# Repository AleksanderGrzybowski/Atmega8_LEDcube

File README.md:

This is a 4x4x4 LED cube made just for the fun of creating it. Cube has been built using the cheapest LEDs on tme.eu, 64 of them, multiplexed: 16 N-driven columns and 4 P-driven layers. Maximum constant and actual diode current is ~50 mA, which makes sure that they won't fail even when multiplexing hangs in the middle while programming. Driver board is made with 3 '595 shift registers, CPU board is using typical Atmega8 family chip.

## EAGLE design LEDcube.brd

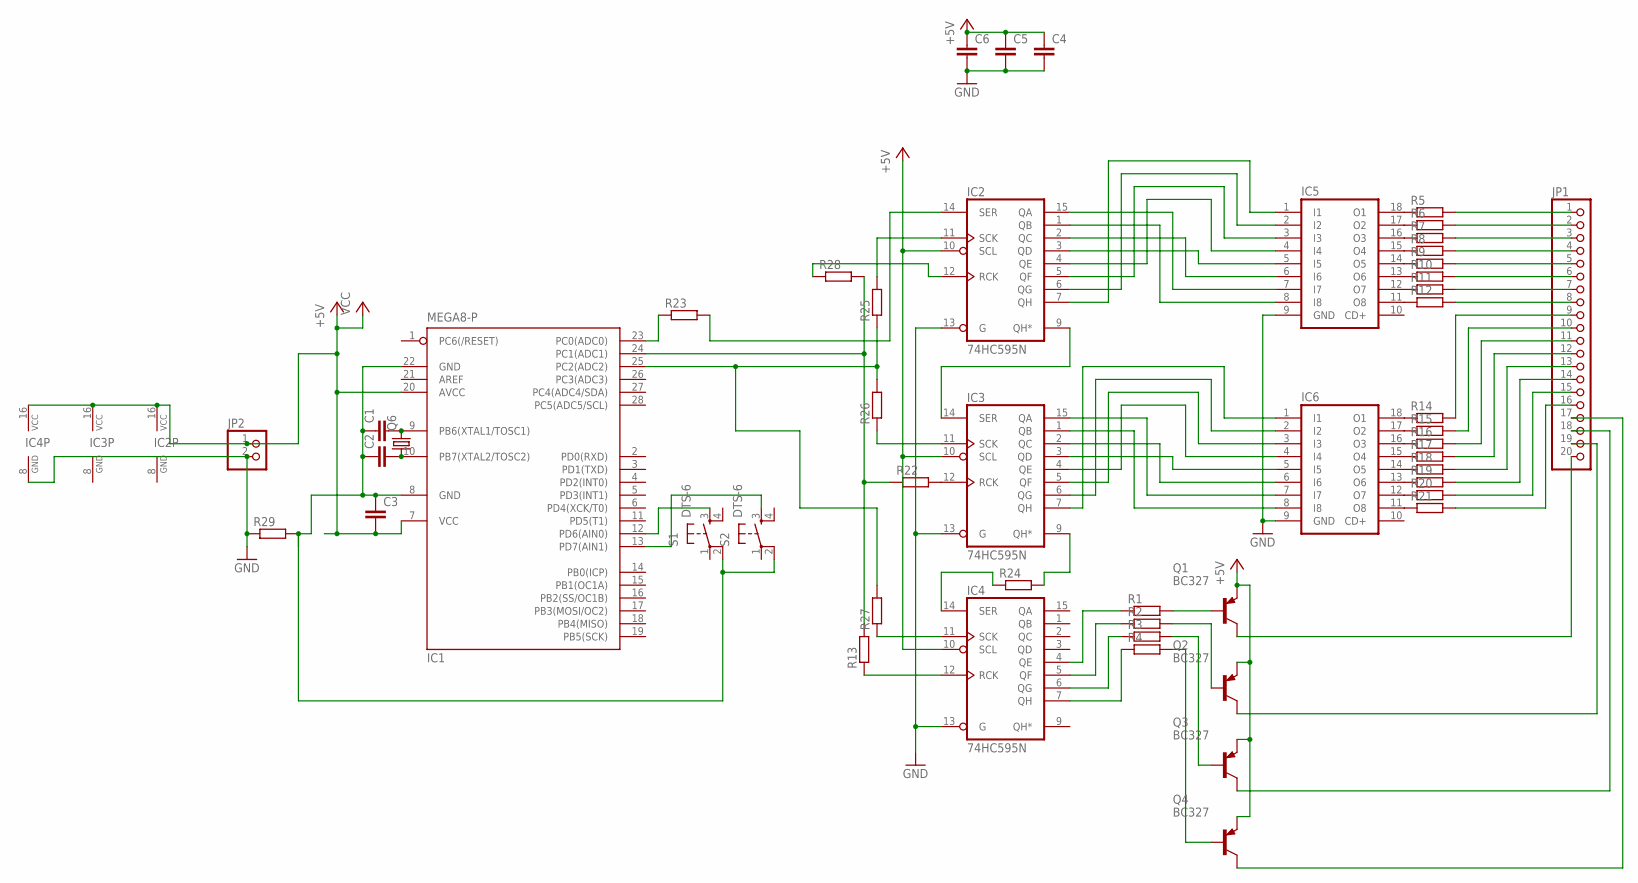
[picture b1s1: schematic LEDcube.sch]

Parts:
C1, C2, C3, C4, C5, C6: C-EU025-024X044; C025-024X044
IC1: MEGA8-P; DIL28-3
IC2, IC3, IC4: 74HC595N; DIL16
IC5, IC6: ULN2803A; DIL18
JP1: PINHD-1X20; 1X20
JP2: PINHD-1X2; 1X02
Q1, Q2, Q3, Q4: BC327; TO92-EBC
Q6: CRYSTALHC18U-V; HC18U-V
R1, R2, R3, R4, R26, R28, R29: R-EU_0204/5; 0204/5
R5, R6, R7, R8, R9, R10, R11, R12, R13, R14, R15, R16, R17, R18, R19, R20, R21, R24, R25, R27: R-EU_0204/2V; 0204V
R22, R23: R-EU_0204/7; 0204/7
S1, S2: DTS-6

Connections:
+5V: C3.2, C4.1, C5.1, C6.1, IC1.7 (VCC), IC1.20 (AVCC), IC2.10 (SCL), IC2.16 (VCC), IC3.10 (SCL), IC3.16 (VCC), IC4.10 (SCL), IC4.16 (VCC), JP2.1, Q1.E, Q2.E, Q3.E, Q4.E
GND: C4.2, C5.2, C6.2, IC2.8 (GND), IC2.13 (G), IC3.8 (GND), IC3.13 (G), IC4.8 (GND), IC4.13 (G), IC5.9 (GND), IC6.9 (GND), JP2.2, R29.1
GND2: C1.1, C2.1, C3.1, IC1.8 (GND), IC1.22 (GND), R29.2, S1.2, S2.2
unnamed: C1.2, IC1.9 (PB6(XTAL1/TOSC1)), Q6.2
unnamed: C2.2, IC1.10 (PB7(XTAL2/TOSC2)), Q6.1
unnamed: IC4.7 (QH), R4.1
unnamed: IC4.6 (QG), R3.1
unnamed: IC4.5 (QF), R2.1
unnamed: IC2.14 (SER), R23.2
unnamed: IC2.9 (QH*), IC3.14 (SER)
unnamed: IC4.14 (SER), R24.1
unnamed: IC1.12 (PD6(AIN0)), S1.3
unnamed: IC1.24 (PC1(ADC1)), R13.2, R22.1, R28.2
unnamed: IC3.9 (QH*), R24.2
unnamed: IC2.1 (QB), IC5.8 (I8)
unnamed: IC2.15 (QA), IC5.7 (I7)
unnamed: IC2.2 (QC), IC5.6 (I6)
unnamed: IC2.3 (QD), IC5.5 (I5)
unnamed: IC2.4 (QE), IC5.4 (I4)
unnamed: IC2.5 (QF), IC5.3 (I3)
unnamed: IC2.6 (QG), IC5.2 (I2)
unnamed: IC2.7 (QH), IC5.1 (I1)
unnamed: IC3.1 (QB), IC6.8 (I8)
unnamed: IC3.15 (QA), IC6.7 (I7)
unnamed: IC3.2 (QC), IC6.6 (I6)
unnamed: IC3.3 (QD), IC6.5 (I5)
unnamed: IC3.4 (QE), IC6.4 (I4)
unnamed: IC3.5 (QF), IC6.3 (I3)
unnamed: IC3.6 (QG), IC6.2 (I2)
unnamed: IC4.4 (QE), R1.1
unnamed: Q1.B, R1.2
unnamed: Q2.B, R2.2
unnamed: Q3.B, R3.2
unnamed: Q4.B, R4.2
unnamed: IC5.18 (O1), R5.1
unnamed: IC5.17 (O2), R6.1
unnamed: IC5.16 (O3), R7.1
unnamed: IC5.15 (O4), R8.1
unnamed: IC5.14 (O5), R9.1
unnamed: IC5.13 (O6), R10.1
unnamed: IC5.12 (O7), R11.1
unnamed: IC5.11 (O8), R12.1
unnamed: JP1.1, R5.2
unnamed: IC6.18 (O1), R14.1
unnamed: IC6.17 (O2), R15.1
unnamed: IC6.16 (O3), R16.1
unnamed: IC6.15 (O4), R17.1
unnamed: IC6.14 (O5), R18.1
unnamed: IC6.13 (O6), R19.1
unnamed: IC6.12 (O7), R20.1
unnamed: IC6.11 (O8), R21.1
unnamed: JP1.2, R6.2
unnamed: JP1.3, R7.2
unnamed: JP1.4, R8.2
unnamed: JP1.5, R9.2
unnamed: JP1.6, R10.2
unnamed: JP1.7, R11.2
unnamed: JP1.8, R12.2
unnamed: JP1.9, R14.2
unnamed: JP1.10, R15.2
unnamed: JP1.11, R16.2
unnamed: JP1.12, R17.2
unnamed: JP1.13, R18.2
unnamed: JP1.14, R19.2
unnamed: JP1.15, R20.2
unnamed: JP1.16, R21.2
unnamed: JP1.20, Q1.C
unnamed: JP1.19, Q2.C
unnamed: JP1.18, Q3.C
unnamed: JP1.17, Q4.C
unnamed: IC3.7 (QH), IC6.1 (I1)
unnamed: IC1.25 (PC2(ADC2)), R25.1, R26.2, R27.2
unnamed: IC1.13 (PD7(AIN1)), S2.3
unnamed: IC1.23 (PC0(ADC0)), R23.1
unnamed: IC4.11 (SCK), R27.1
unnamed: IC3.12 (RCK), R22.2
unnamed: IC2.12 (RCK), R28.1
unnamed: IC4.12 (RCK), R13.1
unnamed: IC3.11 (SCK), R26.1
unnamed: IC2.11 (SCK), R25.2

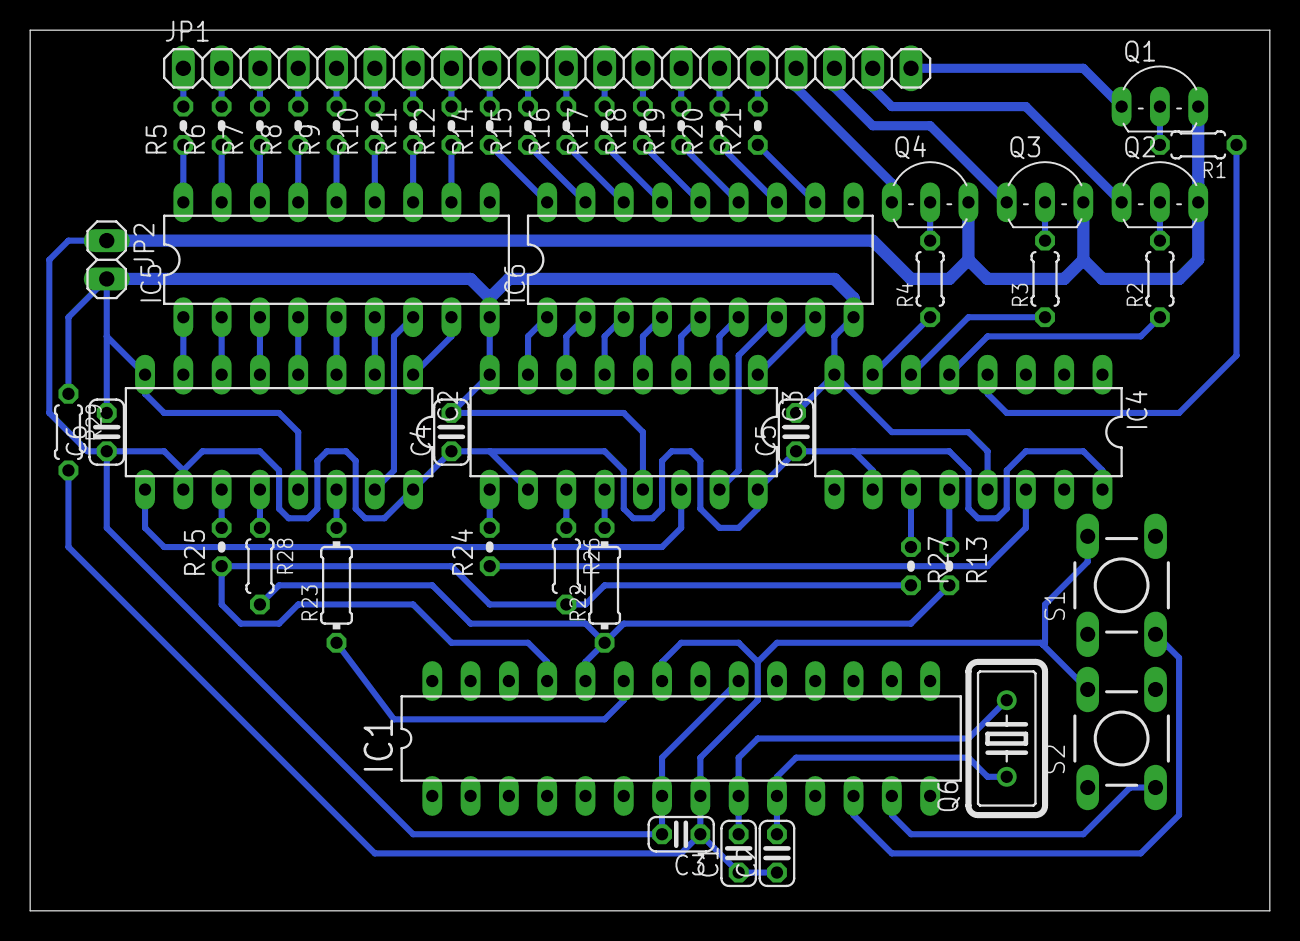
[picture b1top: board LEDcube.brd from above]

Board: 2 copper layers, 82.2 x 58.4 mm, 50 parts (0 on the bottom side), 80 nets.

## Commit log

2015-11-14 Add working Makefile
2015-11-14 595 in separate file, ref
2015-12-02 Photo
2017-03-19 Adjust code to new board
2017-03-31 Eagle schematics and finished thing
2017-04-20 Reformat code, simple button handling
